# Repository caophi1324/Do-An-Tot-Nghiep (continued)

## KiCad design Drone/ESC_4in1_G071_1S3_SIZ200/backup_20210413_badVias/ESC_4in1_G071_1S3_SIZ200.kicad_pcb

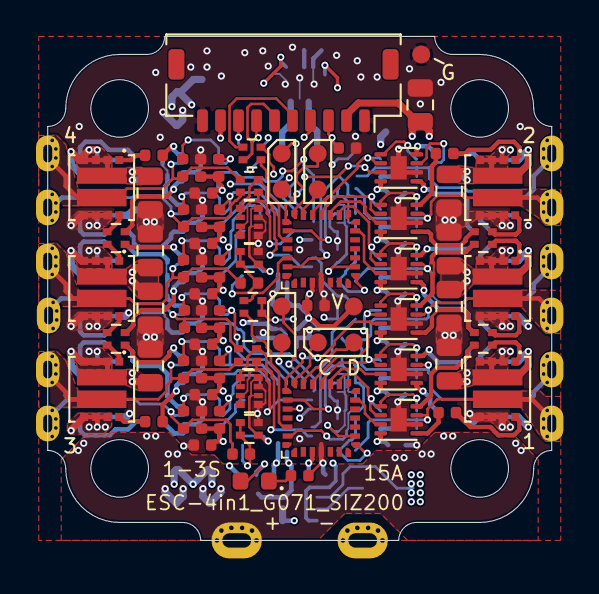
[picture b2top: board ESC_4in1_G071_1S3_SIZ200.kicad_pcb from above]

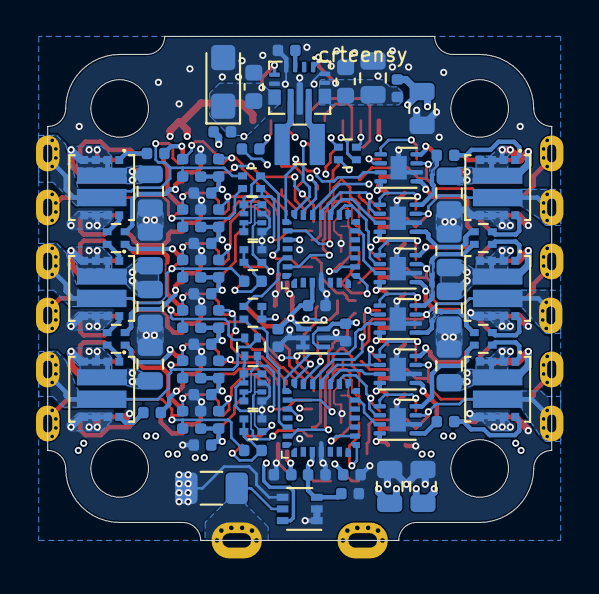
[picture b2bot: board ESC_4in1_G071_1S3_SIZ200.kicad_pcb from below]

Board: 4 copper layers, 28.0 x 28.0 mm, 185 parts (87 on the bottom side), 146 nets.

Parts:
C1, C2, C3, C4, C5, C6, C7, C8, C9, C10, C11, C12, C17, C21, C22, C23, C24, C25, C26, C27, C28, C29, C30, C31, C32, C33, C34, C35, C36, C63: 100n; C_0402_1005Metric
C13: 10u; C_0805_2012Metric_dense
C14, C15: 10u; C_0603_1608Metric_dense
C16: 100u; CP_EIA-3216-10_Kemet-I
C18, C19: 2u2; C_0402_1005Metric
C20: 10n; C_0402_1005Metric
C37, C38, C39, C40, C41, C42, C43, C44, C45, C46, C47, C48, C49, C50, C51, C52, C53, C54, C55, C56: 22u; C_0805_2012Metric_dense
C57, C58, C59, C60, C61, C62, C64, C65, C66, C67, C68, C69, C70: 10u; C_0402_1005Metric
D1: LED; LED_0603_1608Metric
FB1, FB2: Ferrite_Bead_Small; L_0402_1005Metric
H1, H2, H3, H4: MountingHole; MountingHole_3.2mm_4mm
J1: Conn_01x10; JST_SHL_SM10B-SHLS-TF_1x10-1MP_P1.00mm_Horizontal_dense
L1: 820 nH; L_Wuerth_MAPI-2510
R1: 0m5; R_1206_3216Metric
R2, R6, R10, R14, R18: 10k; R_0402_1005Metric
R3, R4, R5, R7, R8, R9, R11, R12, R13, R15, R16, R17: 4k7; R_0402_1005Metric
R19, R20, R21, R22, R23, R24, R25, R26: 10R0; R_0402_1005Metric
R27: 1k; R_0402_1005Metric
RN1, RN3, RN4, RN6, RN14, RN19, RN20, RN22: 10R0; R_Array_Convex_2x0402_dense
RN2, RN5, RN13, RN16: 1k; R_Array_Convex_2x0402_dense
RN7, RN11, RN17, RN23: 2k2; R_Array_Convex_2x0402_dense
RN8, RN10, RN15, RN21: 10k; R_Array_Convex_2x0402_dense
RN9, RN12, RN18, RN24: 2k2; R_Array_Convex_4x0402_dense
TP1, TP2, TP3, TP4, TP5, TP6, TP9, TP10, TP11, TP12, TP13, TP14: TestPoint_Flag; esc_pad_relaxed_n4
TP7, TP8: TestPoint_Flag; batt_pad_wide_relaxed
TP15, TP16, TP17, TP18, TP19, TP20, TP21, TP22, TP23, TP24: TestPoint; TestPoint_Pad_D1.0mm_dense
U1, U17, U21, U28: STM32G071GBU6; UFQFPN28
U2, U4, U6, U8, U10, U12, U18, U20, U23, U25, U27, U30: NCP81161MNTBG; DFN-8-1EP_2x2mm_P0.5mm_EP0.9x1.3mm_narrow
U3, U5, U7, U9, U11, U13, U19, U22, U24, U26, U29, U31: SIZ200DT-T1-GE3; PowerPAIR3.3x3.3_splitpaste
U14: TPS630701; TEXAS_15-VQFN-HR
U15: TPS72733DSE; WSON-6_1.5x1.5mm_P0.5mm
U16: INA186A2; SOT-363_SC-70-6

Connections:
+3V3: C19.2, C21.2, C22.2, C25.2, C32.2, C63.2, C70.2, D1.2, TP23.1, U1.3, U15.1, U16.3, U17.3, U21.3, U28.3
+5V: C4.2, C5.2, C6.2, C7.2, C9.2, C11.2, C18.2, C23.2, C26.2, C28.2, C30.2, C33.2, C35.2, C57.2, C58.2, C59.2, C60.2, C61.2, C62.2, C64.2, C65.2, C66.2, C67.2, C68.2, C69.2, FB2.1, J1.9, R3.1, R4.1, R5.1, R7.1, R8.1, R9.1, R11.1, R12.1, R13.1, R15.1, R16.1, R17.1, U2.4, U4.4, U6.4, U8.4, U10.4, U12.4, U15.4, U15.6, U18.4, U20.4, U23.4, U25.4, U27.4, U30.4
+BATT: C37.2, C38.2, C39.2, C40.2, C41.2, C42.2, C43.2, C44.2, C45.2, C46.2, C47.2, C48.2, C49.2, C50.2, C51.2, C52.2, C53.2, C54.2, C55.2, C56.2, FB1.2, J1.2, TP7.1, U3.2, U5.2, U7.2, U9.2, U11.2, U13.2, U19.2, U22.2, U24.2, U26.2, U29.2, U31.2
/Batt-: R1.2, TP8.1, U16.5
/ESC1_A: C1.1, RN8.2, TP1.1, U2.7, U3.3
/ESC1_A_DRVH: RN6.2, U2.8
/ESC1_A_DRVL: RN1.1, U2.5
/ESC1_A_EN: U1.22, U2.3
/ESC1_A_GH: RN6.3, U3.1
/ESC1_A_GL: RN1.4, U3.5
/ESC1_A_PWM: R3.2, U1.19, U2.2
/ESC1_B: C2.1, RN8.1, TP2.1, U4.7, U5.3
/ESC1_B_DRVH: RN3.1, U4.8
/ESC1_B_DRVL: R26.2, U4.5
/ESC1_B_EN: U1.17, U4.3
/ESC1_B_GH: RN3.4, U5.1
/ESC1_B_GL: R26.1, U5.5
/ESC1_B_PWM: R4.2, U1.18, U4.2
/ESC1_C: C3.1, R6.1, TP3.1, U6.7, U7.3
/ESC1_C_DRVH: RN1.2, U6.8
/ESC1_C_DRVL: R22.2, U6.5
/ESC1_C_EN: U1.13, U6.3
/ESC1_C_GH: RN1.3, U7.1
/ESC1_C_GL: R22.1, U7.5
/ESC1_C_PWM: R5.2, U1.16, U6.2
/ESC1_IN: RN13.4, U1.24
/ESC1_MA: RN8.3, RN9.1, RN9.2, U1.27
/ESC1_MB: RN8.4, RN9.3, RN9.4, U1.23
/ESC1_MC: R6.2, RN7.3, RN7.4, U1.8
/ESC1_SWDCLK: TP22.1, U1.21
/ESC1_SWDIO: TP20.1, U1.20
/ESC1_Y: RN7.1, RN9.6, RN9.8, U1.9
/ESC1_tele_o: RN2.4, U1.26
/ESC2_A: C8.1, RN10.1, TP4.1, U8.7, U9.3
/ESC2_A_DRVH: R19.2, U8.8
/ESC2_A_DRVL: RN4.2, U8.5
/ESC2_A_EN: U8.3, U17.22
/ESC2_A_GH: R19.1, U9.1
/ESC2_A_GL: RN4.3, U9.5
/ESC2_A_PWM: R7.2, U8.2, U17.19
/ESC2_B: C10.1, RN10.2, TP5.1, U10.7, U11.3
/ESC2_B_DRVH: R23.2, U10.8
/ESC2_B_DRVL: RN6.1, U10.5
/ESC2_B_EN: U10.3, U17.17
/ESC2_B_GH: R23.1, U11.1
/ESC2_B_GL: RN6.4, U11.5
/ESC2_B_PWM: R8.2, U10.2, U17.18
/ESC2_C: C12.1, R10.1, TP6.1, U12.7, U13.3
/ESC2_C_DRVH: RN4.1, U12.8
/ESC2_C_DRVL: RN3.2, U12.5
/ESC2_C_EN: U12.3, U17.13
/ESC2_C_GH: RN4.4, U13.1
/ESC2_C_GL: RN3.3, U13.5
/ESC2_C_PWM: R9.2, U12.2, U17.16
/ESC2_IN: RN13.3, U17.24
/ESC2_MA: RN10.4, RN12.1, RN12.2, U17.27
/ESC2_MB: RN10.3, RN12.3, RN12.4, U17.23
/ESC2_MC: R10.2, RN11.3, RN11.4, U17.8
/ESC2_SWDCLK: TP18.1, U17.21
/ESC2_SWDIO: TP16.1, U17.20
/ESC2_Y: RN11.1, RN12.6, RN12.8, U17.9
/ESC2_tele_o: RN2.3, U17.26
/ESC3_A: C31.1, RN21.1, TP12.1, U25.7, U26.3
/ESC3_A_DRVH: RN22.2, U25.8
/ESC3_A_DRVL: RN19.1, U25.5
/ESC3_A_EN: U25.3, U28.22
/ESC3_A_GH: RN22.3, U26.1
/ESC3_A_GL: RN19.4, U26.5
/ESC3_A_PWM: R15.2, U25.2, U28.19
/ESC3_B: C34.1, RN21.2, TP13.1, U27.7, U29.3
/ESC3_B_DRVH: RN20.1, U27.8
/ESC3_B_DRVL: R25.2, U27.5
/ESC3_B_EN: U27.3, U28.17
/ESC3_B_GH: RN20.4, U29.1
/ESC3_B_GL: R25.1, U29.5
/ESC3_B_PWM: R16.2, U27.2, U28.18
/ESC3_C: C36.1, R18.1, TP14.1, U30.7, U31.3
/ESC3_C_DRVH: RN19.2, U30.8
/ESC3_C_DRVL: R21.2, U30.5
/ESC3_C_EN: U28.13, U30.3
/ESC3_C_GH: RN19.3, U31.1
/ESC3_C_GL: R21.1, U31.5
/ESC3_C_PWM: R17.2, U28.16, U30.2
/ESC3_IN: RN16.4, U28.24
/ESC3_MA: RN21.4, RN24.1, RN24.2, U28.27
/ESC3_MB: RN21.3, RN24.3, RN24.4, U28.23
/ESC3_MC: R18.2, RN23.3, RN23.4, U28.8
/ESC3_SWDCLK: TP21.1, U28.21
/ESC3_SWDIO: TP19.1, U28.20
/ESC3_Y: RN23.1, RN24.6, RN24.8, U28.9
/ESC3_tele_o: RN5.4, U28.26
/ESC4_A: C24.1, RN15.1, TP9.1, U18.7, U19.3
/ESC4_A_DRVH: R24.2, U18.8
/ESC4_A_DRVL: RN14.2, U18.5
/ESC4_A_EN: U18.3, U21.22
/ESC4_A_GH: R24.1, U19.1
/ESC4_A_GL: RN14.3, U19.5
/ESC4_A_PWM: R11.2, U18.2, U21.19
/ESC4_B: C27.1, RN15.2, TP10.1, U20.7, U22.3
/ESC4_B_DRVH: R20.2, U20.8
/ESC4_B_DRVL: RN22.1, U20.5
/ESC4_B_EN: U20.3, U21.17
/ESC4_B_GH: R20.1, U22.1
/ESC4_B_GL: RN22.4, U22.5
/ESC4_B_PWM: R12.2, U20.2, U21.18
/ESC4_C: C29.1, R14.1, TP11.1, U23.7, U24.3
/ESC4_C_DRVH: RN14.1, U23.8
/ESC4_C_DRVL: RN20.2, U23.5
/ESC4_C_EN: U21.13, U23.3
/ESC4_C_GH: RN14.4, U24.1
/ESC4_C_GL: RN20.3, U24.5
/ESC4_C_PWM: R13.2, U21.16, U23.2
/ESC4_IN: RN16.3, U21.24
/ESC4_MA: RN15.4, RN18.1, RN18.2, U21.27
/ESC4_MB: RN15.3, RN18.3, RN18.4, U21.23
/ESC4_MC: R14.2, RN17.3, RN17.4, U21.8
/ESC4_SWDCLK: TP17.1, U21.21
/ESC4_SWDIO: TP15.1, U21.20
/ESC4_Y: RN17.1, RN18.6, RN18.8, U21.9
/ESC4_tele_o: RN5.3, U21.26
/ESCx_tele: J1.4, RN2.1, RN2.2, RN5.1, RN5.2
/IBat: C20.2, J1.3, R2.1
GND: C4.1, C5.1, C6.1, C7.1, C9.1, C11.1, C13.1, C14.1, C15.1, C16.2, C17.1, C18.1, C19.1, C20.1, C21.1, C22.1, C23.1, C25.1, C26.1, C28.1, C30.1, C32.1, C33.1, C35.1, C37.1, C38.1, C39.1, C40.1, C41.1, C42.1, C43.1, C44.1, C45.1, C46.1, C47.1, C48.1, C49.1, C50.1, C51.1, C52.1, C53.1, C54.1, C55.1, C56.1, C57.1, C58.1, C59.1, C60.1, C61.1, C62.1, C63.1, C64.1, C65.1, C66.1, C67.1, C68.1, C69.1, C70.1, J1.1, J1.10, R1.1, R27.1, RN7.2, RN9.5, RN9.7, RN11.2, RN12.5, RN12.7, RN17.2, RN18.5, RN18.7, RN23.2, RN24.5, RN24.7, TP24.1, U1.4, U2.6, U2.9, U3.4, U4.6, U4.9, U5.4, U6.6, U6.9, U7.4, U8.6, U8.9, U9.4, U10.6, U10.9, U11.4, U12.6, U12.9, U13.4, U14.4, U14.6, U14.10, U14.15, U15.2, U15.3, U15.5, U16.1, U16.2, U16.4, U17.4, U18.6, U18.9, U19.4, U20.6, U20.9, U21.4, U22.4, U23.6, U23.9, U24.4, U25.6, U25.9, U26.4, U27.6, U27.9, U28.4, U29.4, U30.6, U30.9, U31.4
unnamed: C1.2, U2.1
unnamed: C2.2, U4.1
unnamed: C3.2, U6.1
unnamed: C8.2, U8.1
unnamed: C10.2, U10.1
unnamed: C12.2, U12.1
unnamed: C13.2, C14.2, FB1.1, U14.1, U14.13, U14.14
unnamed: C15.2, C16.1, FB2.2, U14.5, U14.7
unnamed: C17.2, U14.3
unnamed: C24.2, U18.1
unnamed: C27.2, U20.1
unnamed: C29.2, U23.1
unnamed: C31.2, U25.1
unnamed: C34.2, U27.1
unnamed: C36.2, U30.1
unnamed: D1.1, R27.2
unnamed: J1.5, RN13.1
unnamed: J1.6, RN13.2
unnamed: J1.7, RN16.1
unnamed: J1.8, RN16.2
unnamed: L1.1, U14.9
unnamed: L1.2, U14.11
unnamed: R2.2, U16.6
